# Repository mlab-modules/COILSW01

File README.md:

# COILSW01A -  Coil switch

Module for induction solenoid switching up to 48 V DC

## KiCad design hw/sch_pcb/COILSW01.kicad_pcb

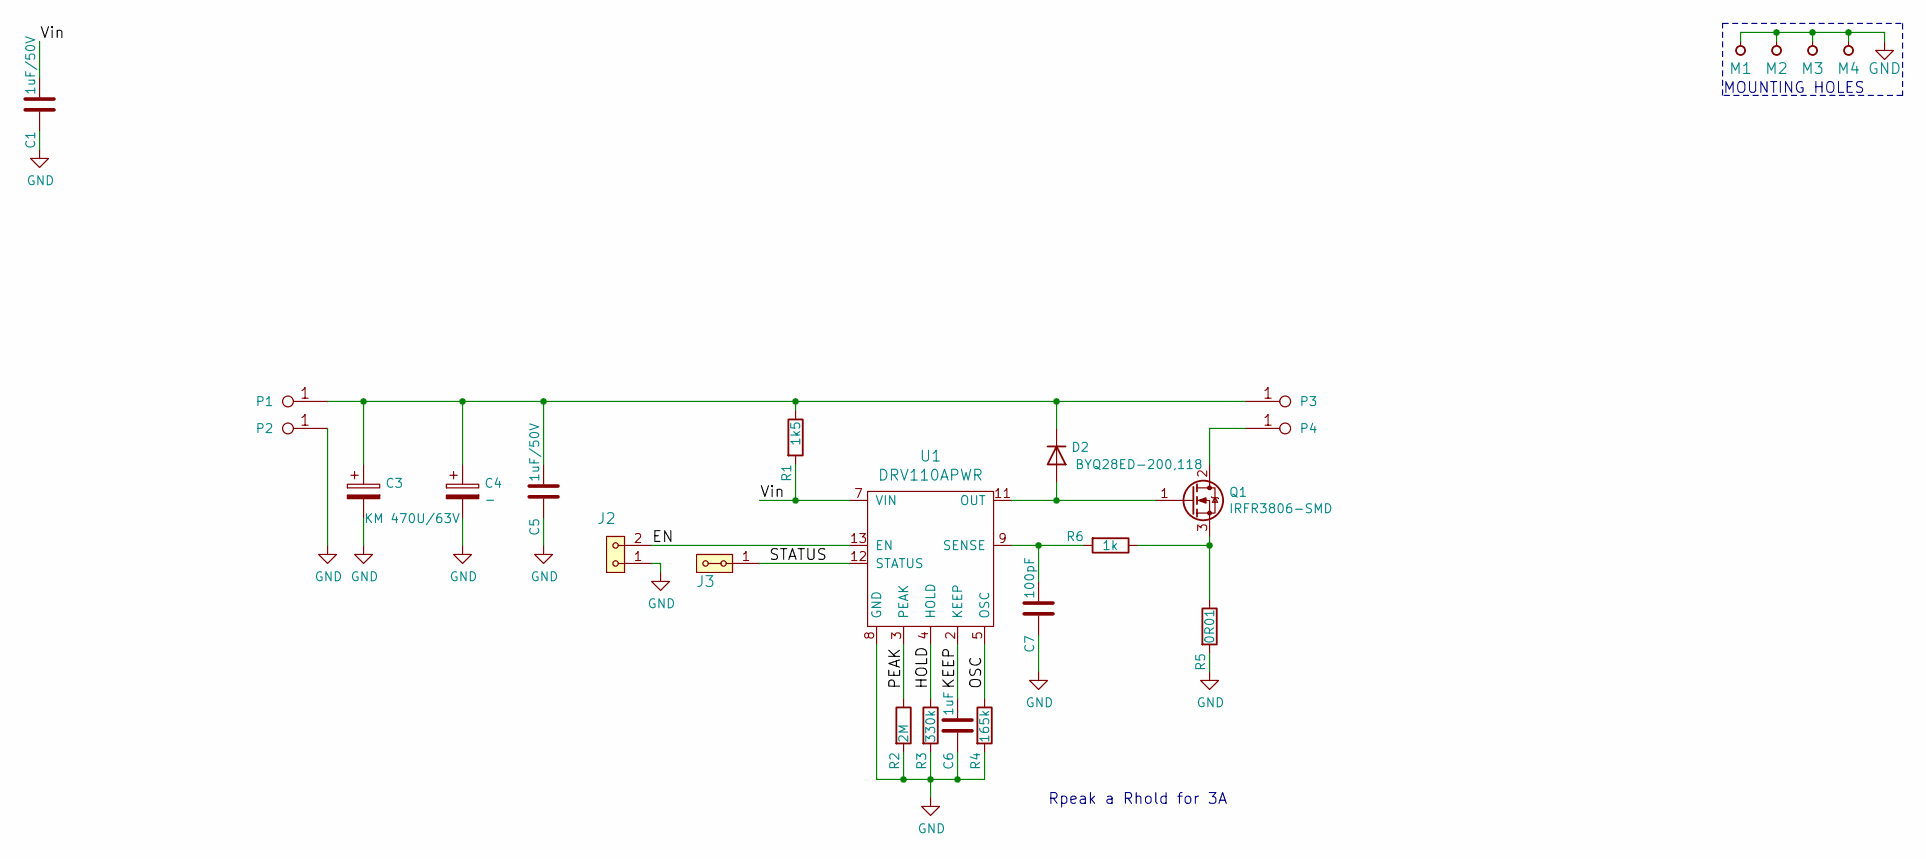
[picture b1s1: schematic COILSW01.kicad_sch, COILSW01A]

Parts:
C1, C5: 1uF/50V; SMD-0805
C3: KM 470U/63V; CP_Radial_D12.5mm_P5.00mm
C4: -; TantalC_SizeD_Reflow
C6: 1uF; SMD-0805
C7: 100pF; SMD-0805
D2: BYQ28ED-200,118; BYQ28ED-200
J2: HEADER_1x02; Straight_1x02
J3: HEADER_2x01_PARALLEL; Straight_1x02
M1, M2, M3, M4: HOLE; MountingHole_3mm
P1, P3, P4: WAGO256-RED; WAGO256
P2: WAGO256-BLUE; WAGO256
Q1: IRFR3806-SMD; TO-252-2
R1: 1k5; SMD-0805
R2: 2M; SMD-0805
R3: 330k; SMD-0805
R4: 165k; SMD-0805
R5: 0R01; SMD-2512
R6: 1k; SMD-0805
U1: DRV110APWR; TSSOP-14_4.4x5mm_P0.65mm

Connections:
/EN: J2.2, U1.13 (EN)
/HOLD: R3.1, U1.4 (HOLD)
/KEEP: C6.1, U1.2 (KEEP)
/OSC: R4.1, U1.5 (OSC)
/PEAK: R2.1, U1.3 (PEAK)
/STATUS: J3.1, J3.2, U1.12 (STATUS)
/Vin: C1.1, R1.2, U1.7 (VIN)
GND: C1.2, C3.2, C4.2, C5.2, C6.2, C7.2, J2.1, M1.1, M2.1, M3.1, M4.1, P2.1, R2.2, R3.2, R4.2, R5.2, U1.8 (GND)
unnamed: C3.1, C4.1, C5.1, D2.1 (K), P1.1, P3.1, R1.1
unnamed: C7.1, R6.2, U1.9 (SENSE)
unnamed: D2.2 (A), Q1.1 (G), U1.11 (OUT)
unnamed: P4.1, Q1.2 (D)
unnamed: Q1.3 (S), R5.1, R6.1

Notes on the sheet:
Rpeak a Rhold for 3A
MOUNTING HOLES

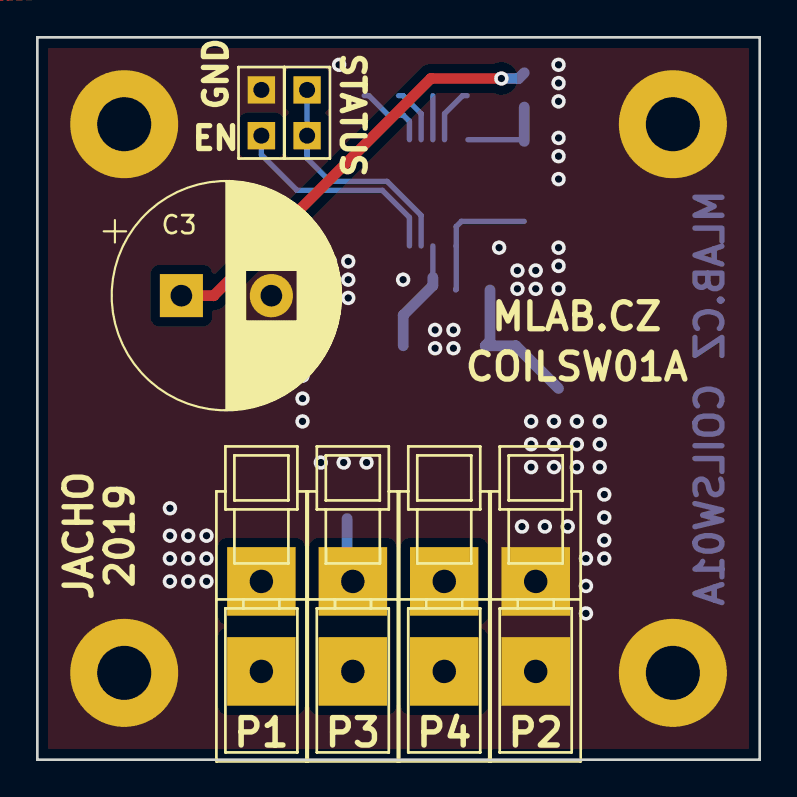
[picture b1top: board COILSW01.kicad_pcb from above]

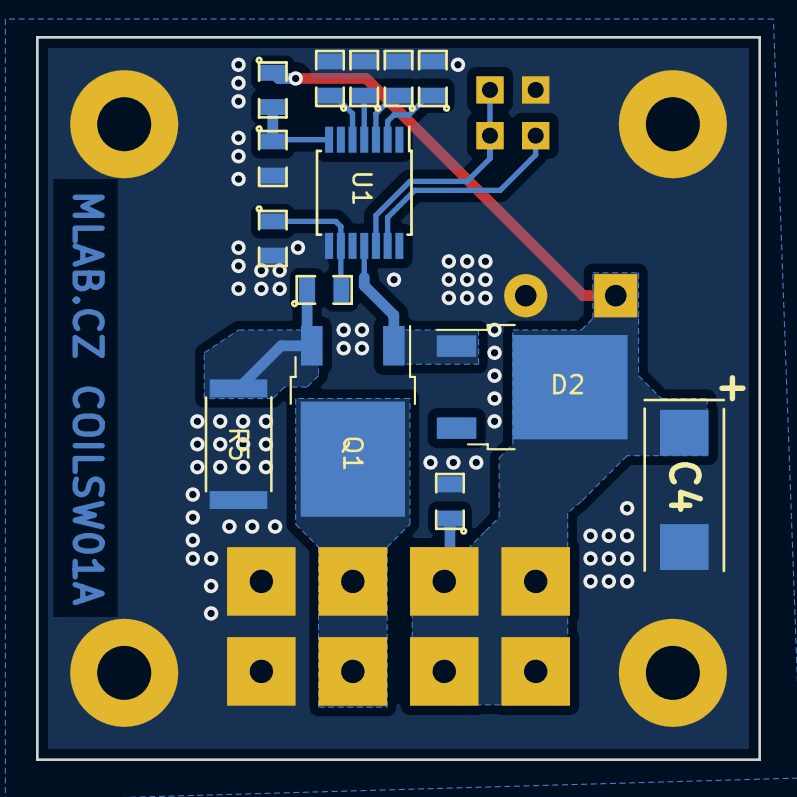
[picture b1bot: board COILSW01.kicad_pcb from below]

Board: 2 copper layers, 40.1 x 40.1 mm, 25 parts (14 on the bottom side), 13 nets.

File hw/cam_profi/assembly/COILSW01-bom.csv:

Component,Description,Part,References,Value,Footprint,Quantity Per PCB,Datasheet,ust_id
1,Unpolarized capacitor,C,C7,100pF,SMD-0805,1,~,5c70984712875079b91f8b3b
2,Unpolarized capacitor,C,C6,1uF,SMD-0805,1,~,5c70984712875079b91f8b6f
3,,CP-Device,C4,-,TantalC_SizeD_Reflow,1,,
4,Unpolarized capacitor,C,C1C5,1uF/50V,SMD-0805,2,~,5c70984712875079b91f8b6f
5,,CP-Device,C3,KM 470U/63V,CP_Radial_D12.5mm_P5.00mm,1,,5c70984412875079b91f886f
6,Diode,D,D2,"BYQ28ED-200,118",BYQ28ED-200,1,~,5c7272001287500b4e112fd9
7,,HEADER_1x02-MLAB_HEADER,J2,HEADER_1x02,Straight_1x02,1,,
8,,HEADER_2x01_PARALLEL-MLAB_HEADER,J3,HEADER_2x01_PARALLEL,Straight_1x02,1,,
9,,_-MLAB_Jumpers,P2,WAGO256-BLUE,WAGO256,1,,
10,,_-MLAB_Jumpers,P1P3P4,WAGO256-RED,WAGO256,3,,
11,"N-MOSFET transistor, gate/drain/source",Q_NMOS_GDS,Q1,IRFR3806-SMD,TO-252-2,1,~,5c70984712875079b91f8aed
12,Resistor,R,R5,0R01,SMD-2512,1,~,5c70984712875079b91f8abf
13,Resistor,R,R6,1k,SMD-0805,1,~,5c70984512875079b91f898c
14,Resistor,R,R1,1k5,SMD-0805,1,~,5c70984512875079b91f898e
15,Resistor,R,R4,165k,SMD-0805,1,~,5c70984712875079b91f8a9b
16,Resistor,R,R3,330k,SMD-0805,1,~,5c70984712875079b91f8aa1
17,Resistor,R,R2,2M,SMD-0805,1,~,5c70984712875079b91f8aac
18,,DRV110APWR-MLAB_IO,U1,DRV110APWR,TSSOP-14_4.4x5mm_P0.65mm,1,,5c72713b1287500b4e112fbc

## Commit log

2023-04-01 Adding force option to enable splitting in not fresh copy of Modules repository.
2023-09-17 automated commit; add github actions
2023-09-17 Update workflow files
2023-09-17 Update metadata files
2024-07-06 Update project to KiCADv7.
2024-07-06 Update actions products
2024-07-06 Update documentation.
